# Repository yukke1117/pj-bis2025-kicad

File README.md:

# af-pj-bis2025

精密アナログ信号処理・データ取得回路のKiCadプロジェクト

## 概要

本プロジェクトは、高精度アナログ信号の取得・調整を目的とした回路基板設計です。24ビットADCを中心に、低ノイズ電源回路とオペアンプによる信号調整回路を組み合わせています。STM32マイコンとの接続を想定した拡張基板として設計されています。

## 主要スペック

- **ADC**: ADS1220IPW (24-bit, TI)
- **オペアンプ**: OPA2380AIDGKR (デュアル), THS4552IPWR (全差動)
- **電圧リファレンス**: REF5050IDR (5V), ADR130BUJZ-REEL7 (精密)
- **電源IC**: MIC5237-5.0YT (5V LDO), UA78L06ACPK (6Vリニアレギュレータ)
- **MOSFET**: ALD114904APAL (低閾値)
- **精密アンプ**: LT1991ACMS-TRPBF
- **コネクタ**: FH28-10S-0.5SH (FPC), SMAコネクタ x2, CN7/CN10 (STM32 Nucleo互換)

## ディレクトリ構成

```
pj-bis2025-kicad/
├── af-pj-bis2025.kicad_pro      # プロジェクトファイル
├── af-pj-bis2025.kicad_sch      # 回路図
├── af-pj-bis2025.kicad_pcb      # PCBレイアウト
├── af-pj-bis2025.kicad_prl      # プロジェクトローカル設定
├── af-pj-bis2025.csv            # 部品表 (BOM)
├── af-pj-bis2025.glb            # 3Dモデル (GLB形式)
├── freerouting.dsn              # 自動配線用ファイル
├── af-pj-bis2025-backups/       # バックアップファイル
├── pj-bis2025.pretty/           # カスタムフットプリントライブラリ
├── pj-bis2025.kicad_sym         # カスタムシンボルライブラリ
├── ultralibrary_zip/            # コンポーネントライブラリ (Ultra Librarian)
├── step/                        # 3Dモデルファイル (STEP形式)
├── stm32/                       # STM32関連サブプロジェクト
│   ├── stm32.kicad_sch          # STM32回路図
│   └── stm32.kicad_pcb          # STM32 PCBレイアウト
├── production/                  # JLCPCB製造用ファイル
│   ├── af-pj-bis2025.zip        # ガーバーファイル一式
│   ├── bom.csv                  # 部品表
│   ├── positions.csv            # 実装位置データ
│   └── netlist.ipc              # IPCネットリスト
└── jlcpcb/                      # JLCPCB製造設定
```

## カスタムライブラリ

### pj-bis2025.pretty (フットプリント)

| フットプリント | 説明 |
|--------------|------|
| ADS1220-PW16-M | ADC (TSSOP-16) |
| OPA2380-DGK8-M | デュアルオペアンプ (VSSOP-8) |
| THS4552-PW0016A_M | 全差動アンプ (TSSOP-16) |
| REF5050-D8-M | 電圧リファレンス (SOIC-8) |
| LT1991-MSOP-10_MS_LIT-M | 精密アンプ (MSOP-10) |
| MIC5237_5_0YT | 5V LDO (SOT-223) |
| UA78L06ACPK-PK0003A_M | 6Vレギュレータ (SOT-89) |
| ADR130BUJZ_REEL7 | 精密電圧リファレンス (SOT-23) |
| ALD114904APAL-8-PDIP_ALD | MOSFET (PDIP-8) |
| HIROSE_FH28-10S-0.5SH_05_ | FPCコネクタ |
| PTS_647_SN50_SMTR2_LFS | プッシュボタンスイッチ |

### ultralibrary_zip (Ultra Librarian)

Ultra Librarianからダウンロードしたコンポーネントライブラリを含みます。

## 必要環境

- **KiCad 9.0** 以上

## 設計ルール

| 項目 | 値 |
|------|-----|
| 最小トラック幅 | 0.25mm |
| 最小クリアランス | 0.2mm |
| ビア径 | 0.6mm |
| ビアドリル | 0.3mm |
| 最小ホールクリアランス | 0.28mm |
| エッジクリアランス | 0.5mm |

## 製造

製造ファイルは `production/` ディレクトリに出力済みです。JLCPCB向けの以下のファイルが含まれています:

- `af-pj-bis2025.zip` - ガーバーファイル一式
- `bom.csv` - 部品表 (SMT実装用)
- `positions.csv` - 部品配置データ (SMT実装用)

## ライセンス

senserity

## 更新履歴

- 2025-01-23: 基板完成、DRCエラーフリー
- 2025-01-20: GNDベタ配置、アナログ配線完了
- 2025-01-19: アノテーション再定義、フットプリント更新
- 2025-01-18: PCBレイアウト変更
- 2024-11-24: 初期設計

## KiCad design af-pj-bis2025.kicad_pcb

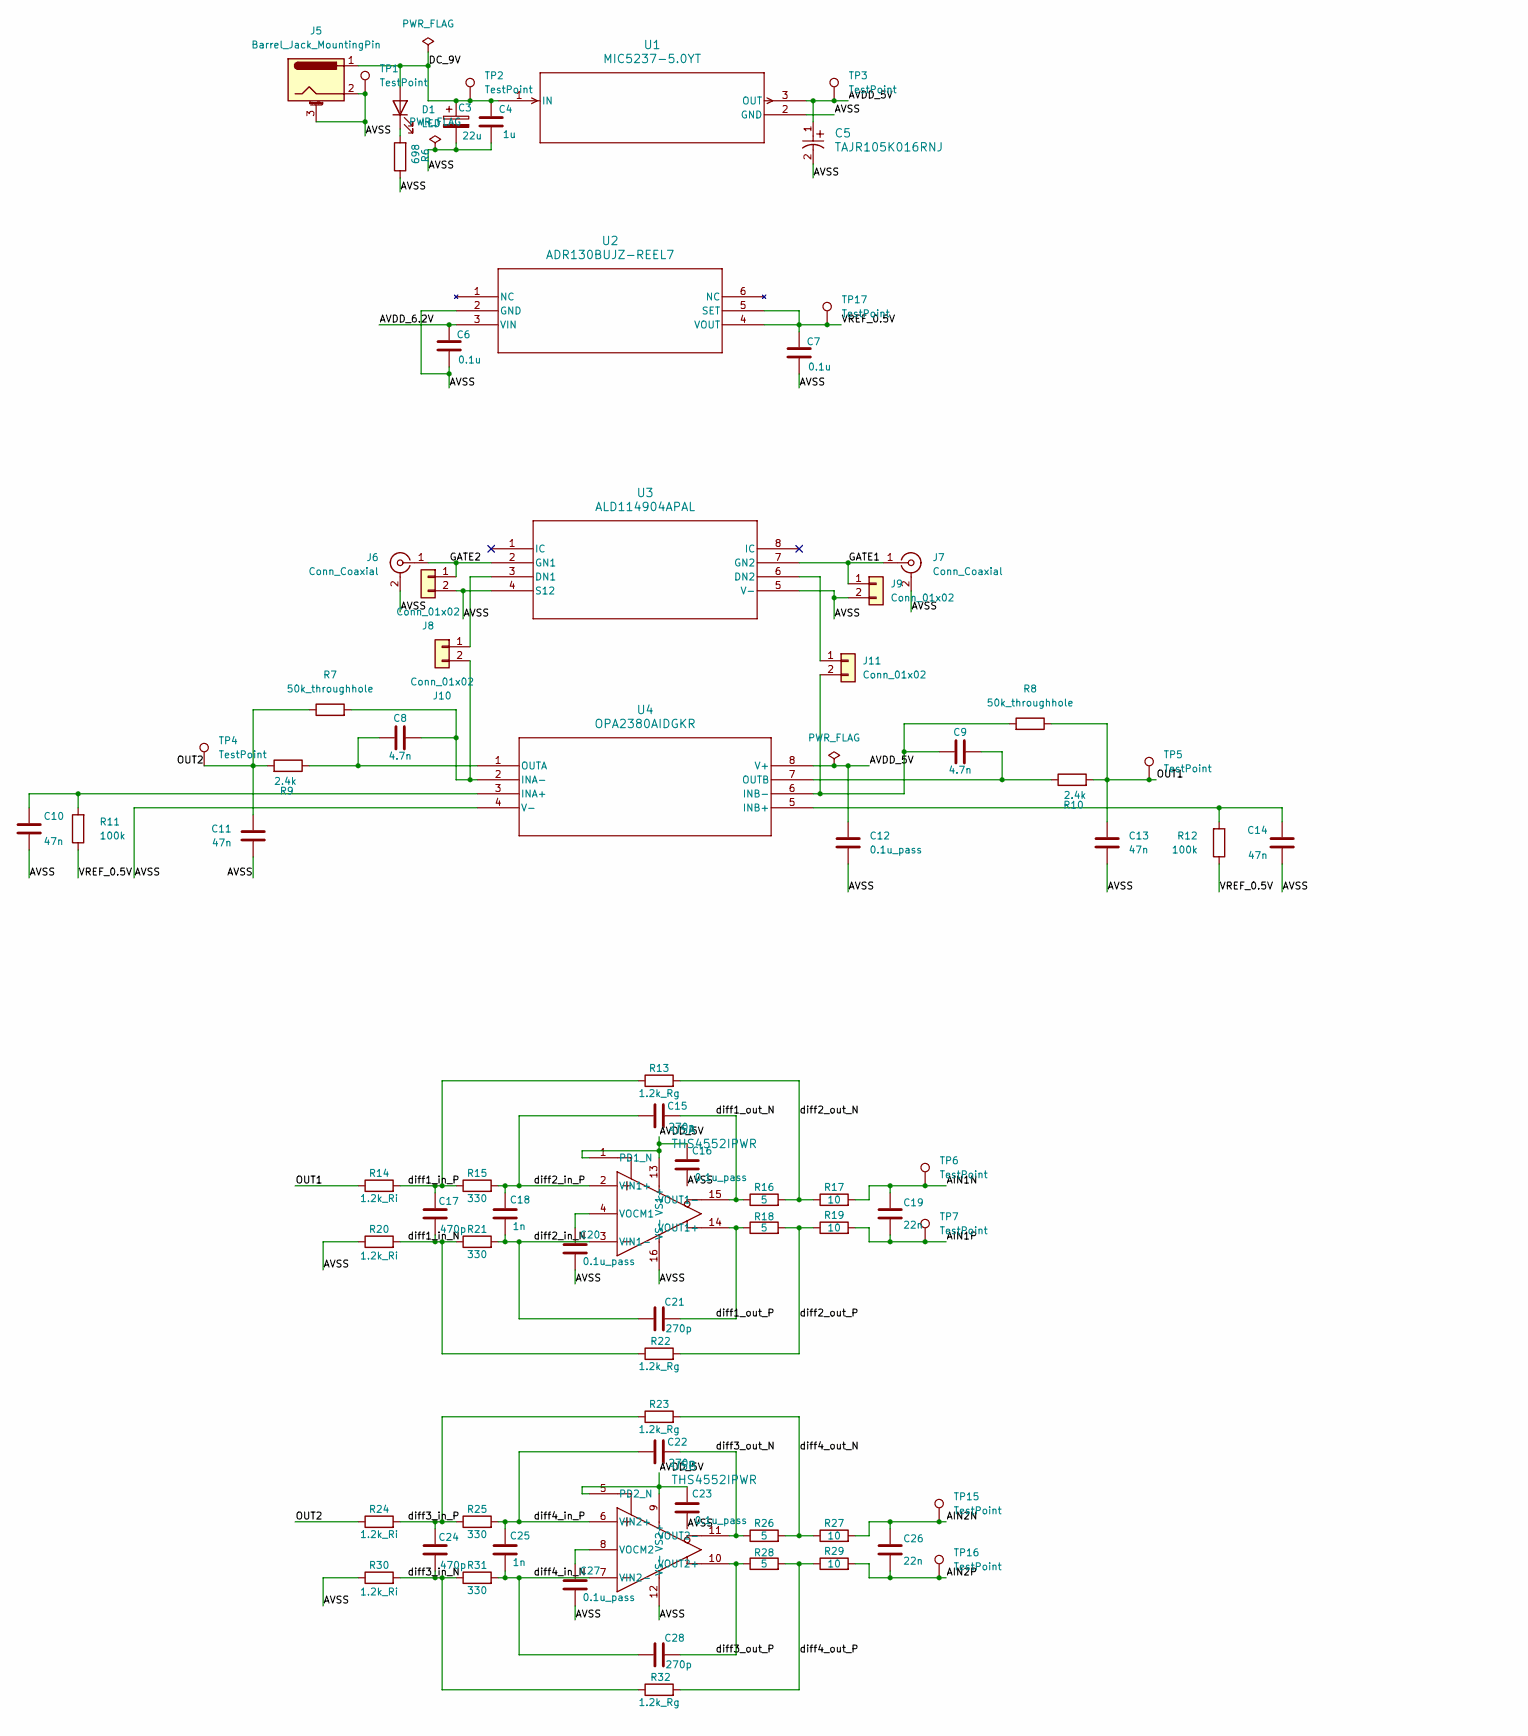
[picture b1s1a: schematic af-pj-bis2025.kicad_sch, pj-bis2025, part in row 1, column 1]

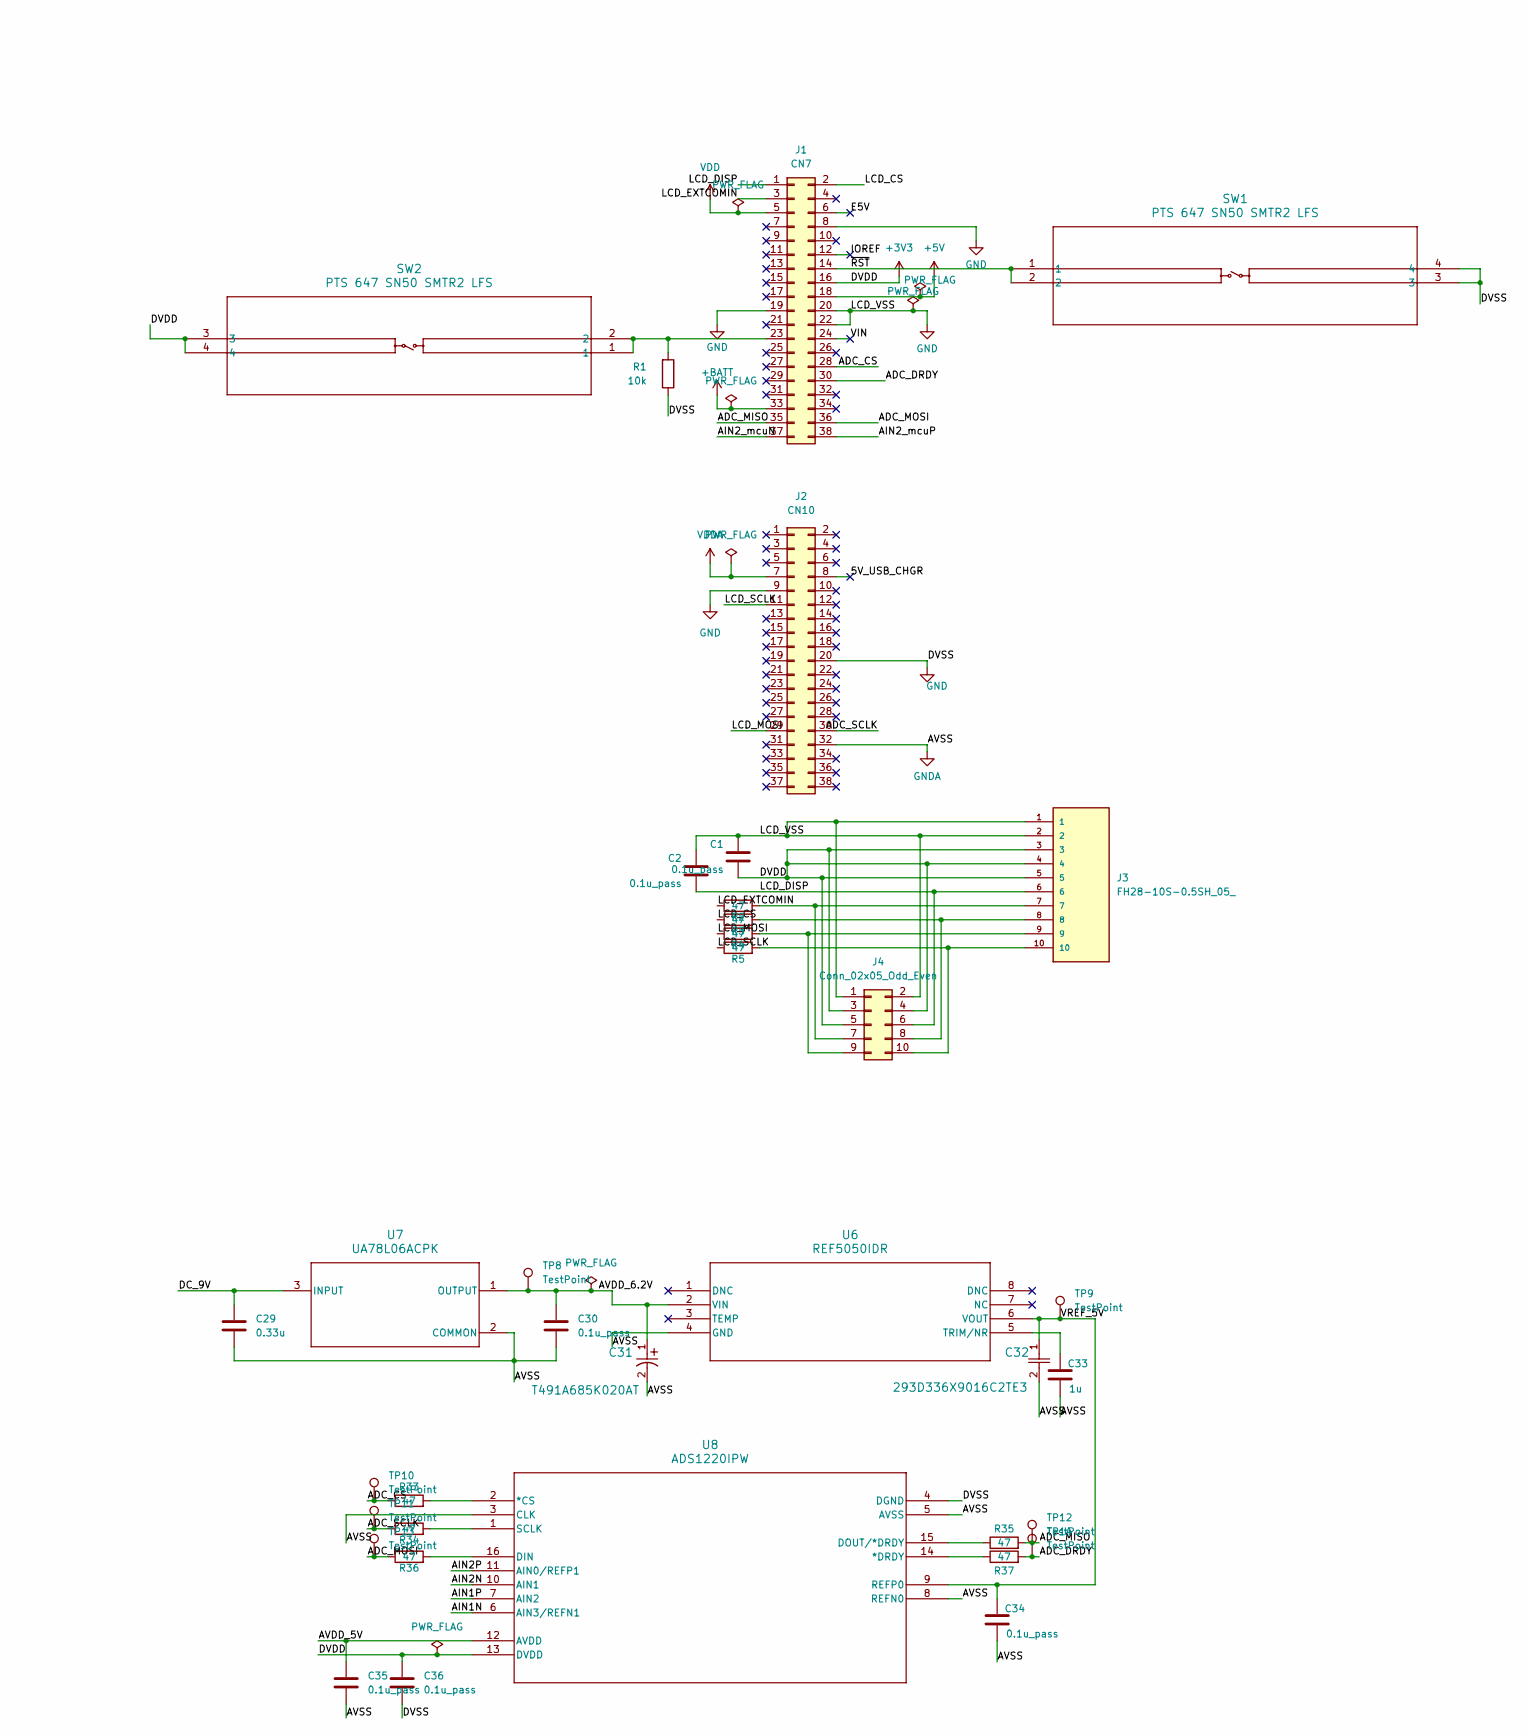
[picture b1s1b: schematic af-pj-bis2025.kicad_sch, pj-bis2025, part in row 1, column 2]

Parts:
C1, C2, C12, C16, C20, C23, C27, C30, C34, C35, C36: 0.1u_pass; C_0805_2012Metric_Pad1.18x1.45mm_HandSolder
C3: 22u; CP_EIA-3528-15_AVX-H_HandSolder
C4, C33: 1u; C_0805_2012Metric_Pad1.18x1.45mm_HandSolder
C5: TAJR105K016RNJ; C_0805_2012Metric_Pad1.18x1.45mm_HandSolder
C6, C7: 0.1u; C_0805_2012Metric_Pad1.18x1.45mm_HandSolder
C8, C9: 4.7n; C_0805_2012Metric_Pad1.18x1.45mm_HandSolder
C10, C11, C13, C14: 47n; C_0805_2012Metric_Pad1.18x1.45mm_HandSolder
C15, C21, C22, C28: 270p; C_0805_2012Metric_Pad1.18x1.45mm_HandSolder
C17, C24: 470p; C_0805_2012Metric_Pad1.18x1.45mm_HandSolder
C18, C25: 1n; C_0805_2012Metric_Pad1.18x1.45mm_HandSolder
C19, C26: 22n; C_0805_2012Metric_Pad1.18x1.45mm_HandSolder
C29: 0.33u; C_0805_2012Metric_Pad1.18x1.45mm_HandSolder
C31: T491A685K020AT; Vref_in_tantal_T491A685K020AT_CAPMP3.4X1.6_1.8N_KEM-M
C32: 293D336X9016C2TE3; Vref_out_tantal_293D336X9016C2TE3_CAP_293D-C_VSS
D1: LED; LED_0805_2012Metric_Pad1.15x1.40mm_HandSolder
J1: CN7; PinSocket_2x19_P2.54mm_Vertical
J2: CN10; PinSocket_2x19_P2.54mm_Vertical
J3: FH28-10S-0.5SH_05_; HIROSE_FH28-10S-0.5SH_05_; PARTREV 13.09.20
J4: Conn_02x05_Odd_Even; PinSocket_2x05_P2.54mm_Vertical
J5: Barrel_Jack_MountingPin; BarrelJack_Horizontal
J6, J7: Conn_Coaxial; SMA_Amphenol_901-143_Horizontal
J8, J9, J10, J11: Conn_01x02; PinHeader_1x02_P2.54mm_Vertical
R1: 10k; R_0805_2012Metric_Pad1.20x1.40mm_HandSolder
R2, R3, R4, R5, R33, R34, R35, R36, R37: 47; R_0805_2012Metric_Pad1.20x1.40mm_HandSolder
R6: 698; R_0805_2012Metric_Pad1.20x1.40mm_HandSolder
R7, R8: 50k_throughhole; R_0805_2012Metric_Pad1.20x1.40mm_HandSolder
R9, R10: 2.4k; R_0805_2012Metric_Pad1.20x1.40mm_HandSolder
R11, R12: 100k; R_0805_2012Metric_Pad1.20x1.40mm_HandSolder
R13, R22, R23, R32: 1.2k_Rg; R_0805_2012Metric_Pad1.20x1.40mm_HandSolder
R14, R20, R24, R30: 1.2k_Ri; R_0805_2012Metric_Pad1.20x1.40mm_HandSolder
R15, R21, R25, R31: 330; R_0805_2012Metric_Pad1.20x1.40mm_HandSolder
R16, R18, R26, R28: 5; R_0805_2012Metric_Pad1.20x1.40mm_HandSolder
R17, R19, R27, R29: 10; R_0805_2012Metric_Pad1.20x1.40mm_HandSolder
SW1, SW2: PTS 647 SN50 SMTR2 LFS; PTS_647_SN50_SMTR2_LFS_PTS 647 SN50 SMTR2 LFS-M
TP1, TP2, TP3, TP4, TP5, TP6, TP7, TP8, TP9, TP10, TP11, TP12, TP13, TP14, TP15, TP16, TP17: TestPoint; Pin_D1.0mm_L10.0mm
U1: MIC5237-5.0YT; MIC5237_5_0YT
U2: ADR130BUJZ-REEL7; ADR130BUJZ_REEL7
U3: ALD114904APAL; ALD114904APAL-8-PDIP_ALD
U4: OPA2380AIDGKR; OPA2380-DGK8-M
U5: THS4552IPWR; THS4552-PW0016A_M
U6: REF5050IDR; REF5050-D8-M
U7: UA78L06ACPK; UA78L06ACPK-PK0003A_M
U8: ADS1220IPW; ADS1220-PW16-M

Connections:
+3V3: C1.1, C36.1, J1.16, J3.3, J3.4, J3.5, J4.3, J4.4, J4.5, SW2.3, SW2.4, U8.13 (DVDD)
+5V: J1.18
+BATT: J1.33
/5V_USB_CHGR: J2.8
/ADC_CS: J1.28, R33.1, TP10.1
/ADC_DRDY: J1.30, R37.2, TP14.1
/ADC_MISO: J1.35, R35.2, TP12.1
/ADC_MOSI: J1.36, R36.1, TP13.1
/ADC_SCLK: J2.30, R34.1, TP11.1
/AIN1N: C19.2, R17.2, TP6.1, U8.6 (AIN3/REFN1)
/AIN1P: C19.1, R19.2, TP7.1, U8.7 (AIN2)
/AIN2N: C26.2, R27.2, TP15.1, U8.10 (AIN1)
/AIN2P: C26.1, R29.2, TP16.1, U8.11 (AIN0/REFP1)
/AIN2_mcuN: J1.37
/AIN2_mcuP: J1.38
/AVDD_5V: C5.1, C12.2, C16.2, C23.2, C35.1, TP3.1, U1.3 (OUT), U4.8 (V+), U5.1 (PD1_N), U5.5 (PD2_N), U5.9 (VS2+), U5.13 (VS1+), U8.12 (AVDD)
/AVDD_6.2V: C6.1, C30.1, C31.1, TP8.1, U2.3 (VIN), U6.2 (VIN), U7.1 (OUTPUT)
/DC_9V: C3.1, C4.1, C29.1, D1.2 (A), J5.1, TP2.1, U1.1 (IN), U7.3 (INPUT)
/E5V: J1.6
/GATE1: J7.1 (In), J9.1, U3.7 (GN2)
/GATE2: J6.1 (In), J8.1, U3.2 (GN1)
/IOREF: J1.12
/LCD_CS: J1.2, R3.1
/LCD_DISP: C2.1, J1.1, J3.6, J4.6
/LCD_EXTCOMIN: J1.3, R2.1
/LCD_MOSI: J2.29, R4.1
/LCD_SCLK: J2.11, R5.1
/OUT1: C13.2, R8.1, R10.2, R14.1, TP5.1
/OUT2: C11.2, R7.1, R9.2, R24.1, TP4.1
/VIN: J1.24
/VREF_0.5V: C7.1, R11.1, R12.1, TP17.1, U2.4 (VOUT), U2.5 (SET)
/VREF_5V: C32.1, C34.1, TP9.1, U6.6 (VOUT), U8.9 (REFP0)
/diff1_in_N: C17.1, R20.2, R21.1, R22.1
/diff1_in_P: C17.2, R13.1, R14.2, R15.1
/diff1_out_N: C15.1, R16.1, U5.15 (VOUT1-)
/diff1_out_P: C21.1, R18.1, U5.14 (VOUT1+)
/diff2_in_N: C18.1, C21.2, R21.2, U5.3 (VIN1-)
/diff2_in_P: C15.2, C18.2, R15.2, U5.2 (VIN1+)
/diff2_out_N: R13.2, R16.2, R17.1
/diff2_out_P: R18.2, R19.1, R22.2
/diff3_in_N: C24.1, R30.2, R31.1, R32.1
/diff3_in_P: C24.2, R23.1, R24.2, R25.1
/diff3_out_N: C22.1, R26.1, U5.11 (VOUT2-)
/diff3_out_P: C28.1, R28.1, U5.10 (VOUT2+)
/diff4_in_N: C25.1, C28.2, R31.2, U5.7 (VIN2-)
/diff4_in_P: C22.2, C25.2, R25.2, U5.6 (VIN2+)
/diff4_out_N: R23.2, R26.2, R27.1
/diff4_out_P: R28.2, R29.1, R32.2
/~RST: J1.14, SW1.1, SW1.2
GND: C1.2, C2.2, C36.2, J1.8, J1.19, J1.20, J1.22, J2.9, J2.20, J3.1, J3.2, J4.1, J4.2, R1.1, SW1.3, SW1.4, U8.4 (DGND)
GNDA: C3.2, C4.2, C5.2, C6.2, C7.2, C10.1, C11.1, C12.1, C13.1, C14.1, C16.1, C20.1, C23.1, C27.1, C29.2, C30.2, C31.2, C32.2, C33.2, C34.2, C35.2, J2.32, J5.2, J5.3 (MountPin), J6.2 (Ext), J7.2 (Ext), J8.2, J9.2, R6.1, R20.1, R30.1, TP1.1, U1.2 (GND), U2.2 (GND), U3.4 (S12), U3.5 (V-), U4.4 (V-), U5.12 (VS-), U5.16 (VS-), U6.4 (GND), U7.2 (COMMON), U8.3 (CLK), U8.5 (AVSS), U8.8 (REFN0)
unnamed: D1.1 (K), R6.2
unnamed: J1.23, R1.2, SW2.1, SW2.2
unnamed: J3.7, J4.7, R2.2
unnamed: J3.8, J4.8, R3.2
unnamed: J3.9, J4.9, R4.2
unnamed: J3.10, J4.10, R5.2
unnamed: J10.1, U3.3 (DN1)
unnamed: C8.2, J10.2, R7.2, U4.2 (INA-)
unnamed: J11.1, U3.6 (DN2)
unnamed: C9.2, J11.2, R8.2, U4.6 (INB-)
unnamed: C10.2, R11.2, U4.3 (INA+)
unnamed: C14.2, R12.2, U4.5 (INB+)
unnamed: C8.1, R9.1, U4.1 (OUTA)
unnamed: C9.1, R10.1, U4.7 (OUTB)
unnamed: C20.2, U5.4 (VOCM1)
unnamed: C27.2, U5.8 (VOCM2)
unnamed: C33.1, U6.5 (TRIM/NR)
unnamed: R33.2, U8.2 (*CS)
unnamed: R37.1, U8.14 (*DRDY)
unnamed: R36.2, U8.16 (DIN)
unnamed: R35.1, U8.15 (DOUT/*DRDY)
unnamed: R34.2, U8.1 (SCLK)
VDD: J1.5
VDDA: J2.7

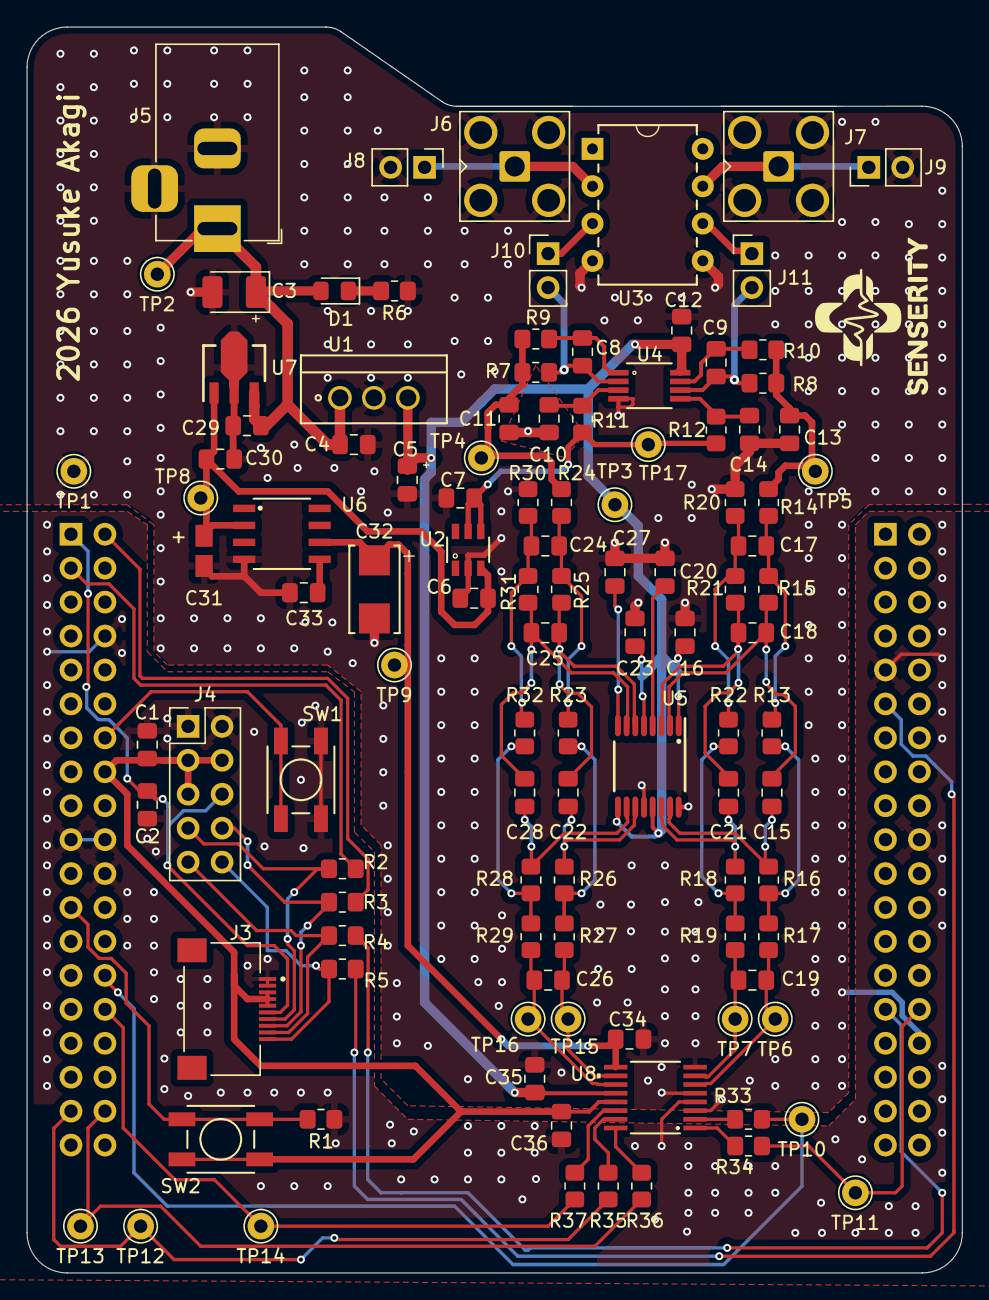
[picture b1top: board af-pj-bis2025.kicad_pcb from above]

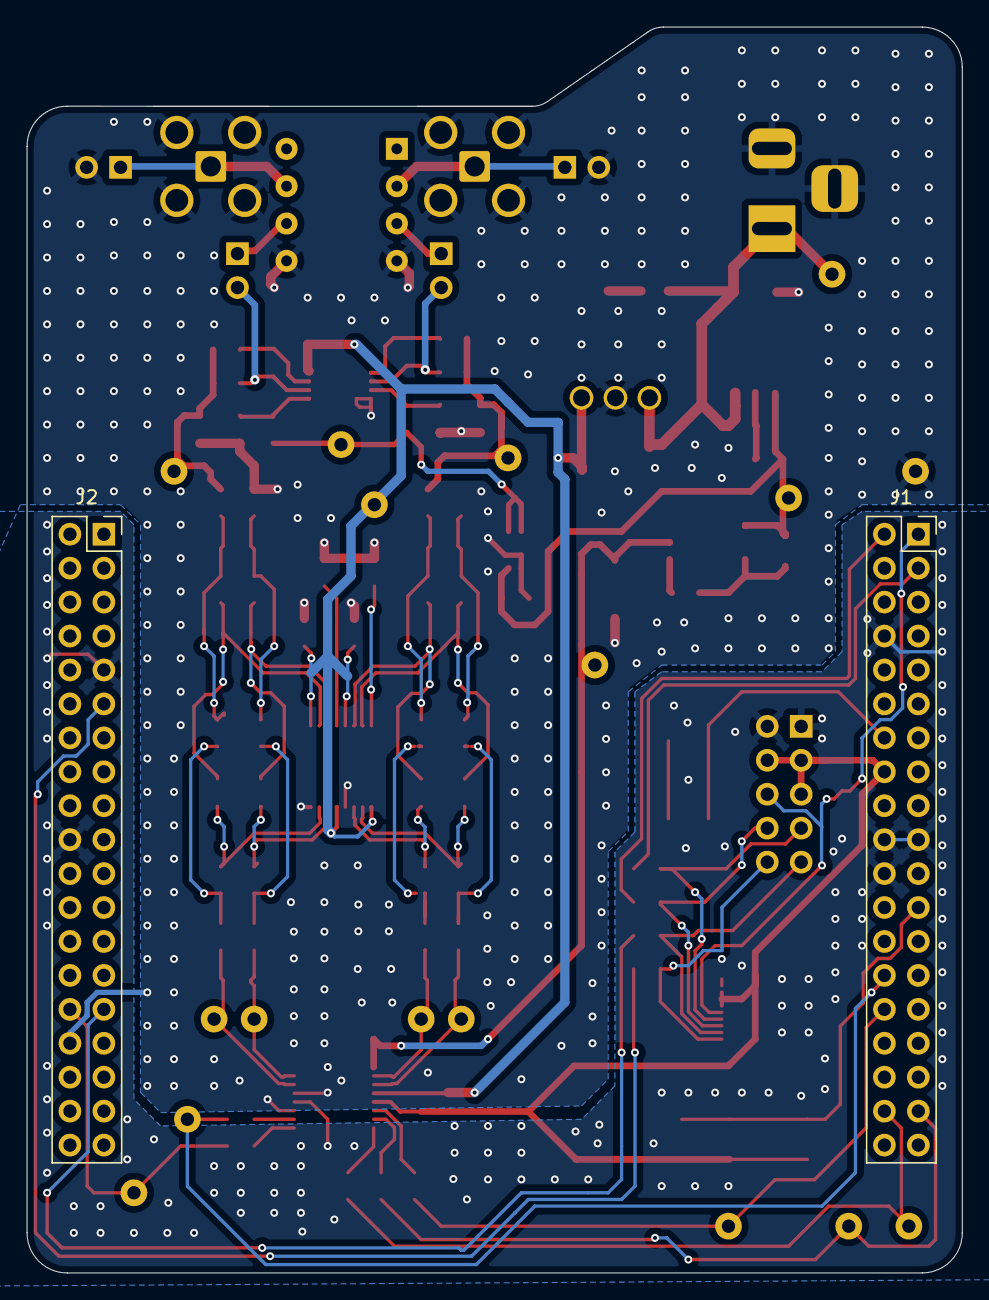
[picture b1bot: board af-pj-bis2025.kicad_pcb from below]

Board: 2 copper layers, 70.0 x 93.2 mm, 112 parts (2 on the bottom side), 65 nets.

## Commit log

2025-12-22 inititl commit
2025-12-22 rm .gitignore
2025-12-22 add .gitignore
2025-12-29 ADC追加
2025-12-30 ERCを解消した1
2025-12-30 ERCエラー修正2
2025-12-30 パスコンを追加
2025-12-30 フットプリントの割り当て
2026-01-02 Uのフットプリント割り当て完了
2026-01-02 アノテーション
2026-01-02 タンタルキャパシタ置き換え、フットプリント割り当て
2026-01-02 キャパシタをタンタルキャパシタに変更した
2026-01-02 フットプリント割り当て完了
2026-01-02 drc設定と、pcbの更新完了
2026-01-03 差動増幅回路のレイアウト完了
2026-01-03 AVSS接続完了
2026-01-03 AVDD-5Vを配線
2026-01-03 LCDの配線完了
2026-01-03 ADCのディジタル配線完了
2026-01-03 EdgeCutsを調整した
2026-01-03 DRC,LVSクリアとテストピン、デバック用ピン追加
2026-01-05 回路が完成した
2026-01-16 add readme
2026-01-18 change PCB layout
2026-01-18 LCDのコネクタ変更(schematic)
2026-01-18 ADCのコネクタ削除(Schematic)
2026-01-18 アノテーションを再定義
2026-01-18 0.5Vrefのフットプリントを更新
2026-01-18 アナログ配線完了
2026-01-18 GND以外終わり
2026-01-18 GNDベタを配置
2026-01-18 savd
2026-01-18 save
2026-01-18 DRCエラーフリー
2026-01-18 基板完成
